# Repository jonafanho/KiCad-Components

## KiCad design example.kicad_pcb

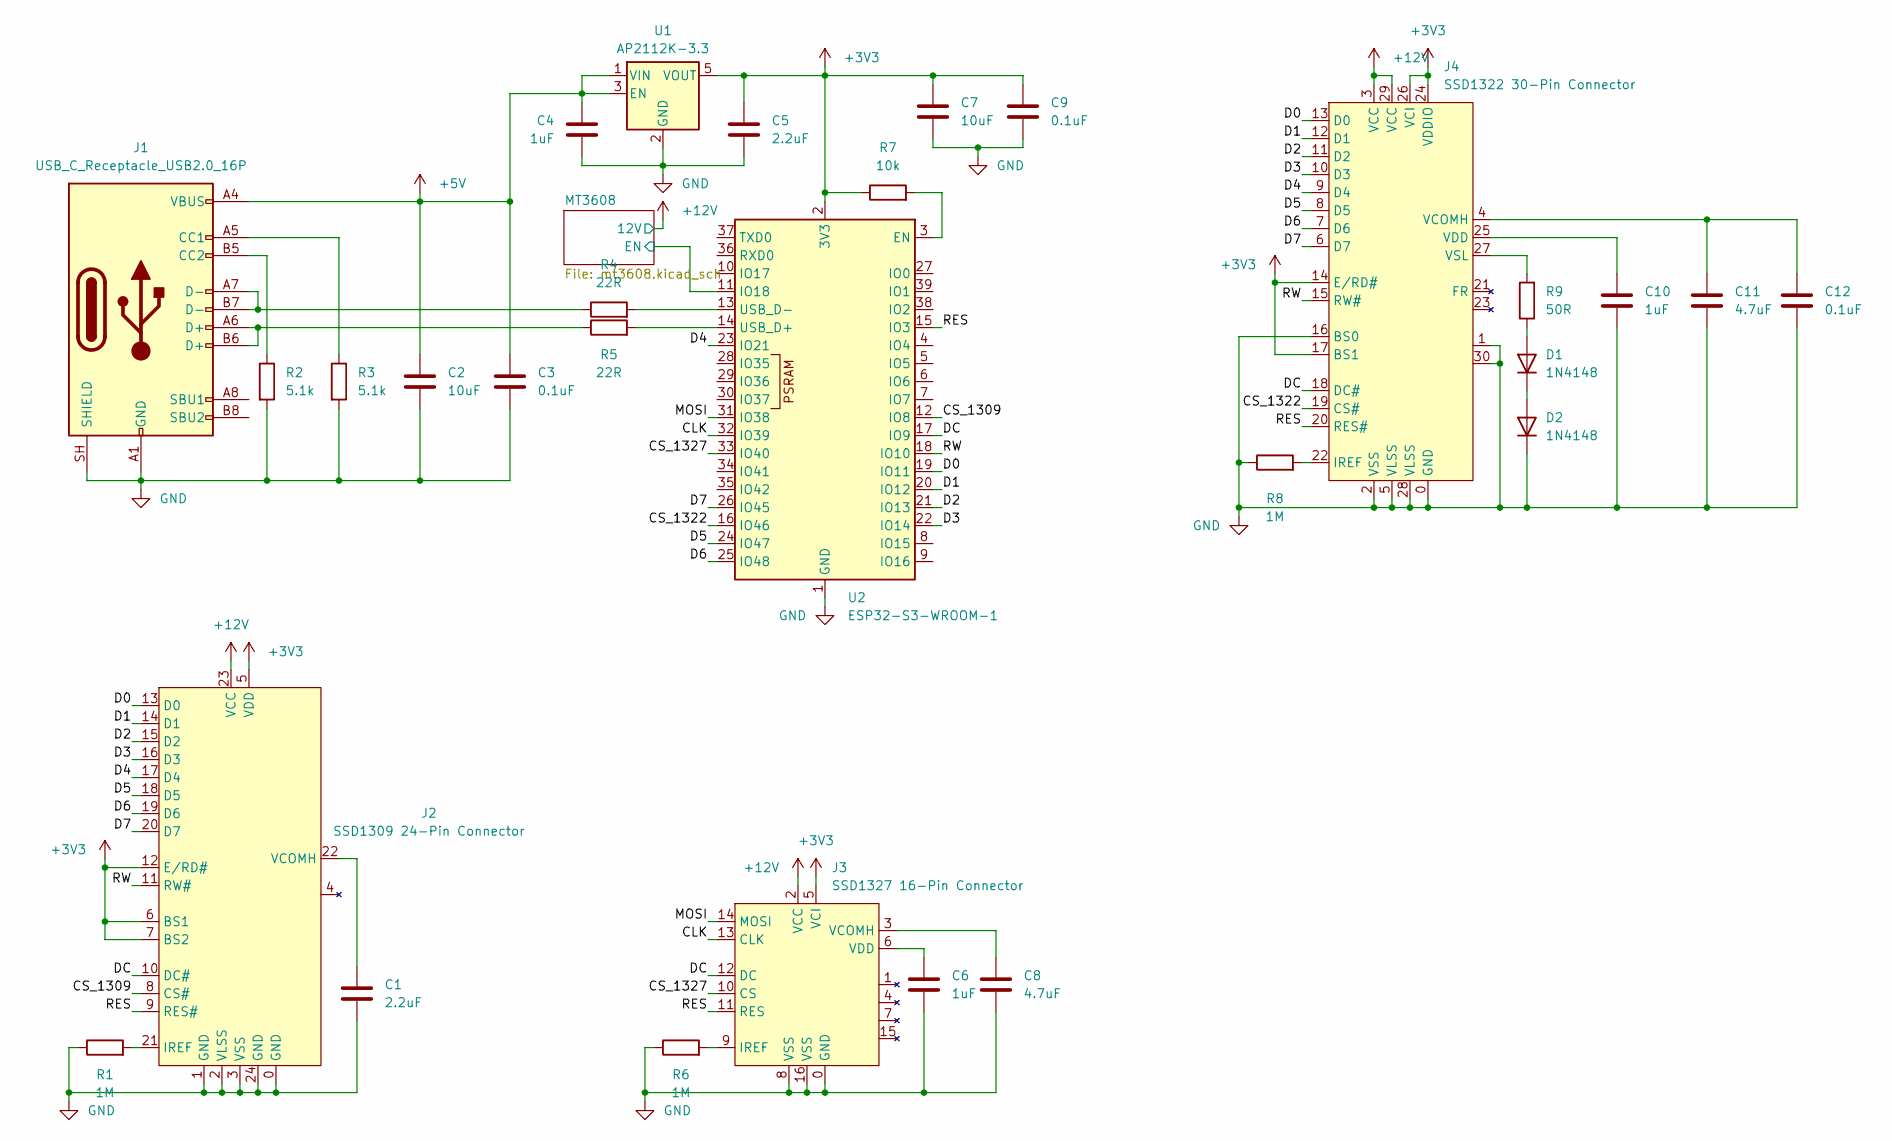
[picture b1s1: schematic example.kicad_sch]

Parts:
C1, C5: 2.2uF; C_0603_1608Metric
C2, C7: 10uF; C_0603_1608Metric
C3, C9, C12: 0.1uF; C_0603_1608Metric
C4, C6, C10: 1uF; C_0603_1608Metric
C8, C11: 4.7uF; C_0603_1608Metric
D1, D2: 1N4148; D_SOD-123
J1: USB_C_Receptacle_USB2.0_16P; USB_C_Receptacle_HCTL_HC-TYPE-C-16P-01A
J2: SSD1309 24-Pin Connector; 24-pin
J3: SSD1327 16-Pin Connector; 16-pin
J4: SSD1322 30-Pin Connector; 30-pin
R1, R6, R8: 1M; R_0603_1608Metric
R2, R3: 5.1k; R_0603_1608Metric
R4, R5: 22R; R_0603_1608Metric
R7: 10k; R_0603_1608Metric
R9: 50R; R_0603_1608Metric
U1: AP2112K-3.3; SOT-23-5
U2: ESP32-S3-WROOM-1

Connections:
+3V3: C5.1, C7.1, C9.1, J2.5 (VDD), J2.6 (BS1), J2.7 (BS2), J2.12 (E/RD#), J3.5 (VCI), J4.14 (E/RD#), J4.17 (BS1), J4.24 (VDDIO), J4.26 (VCI), R7.1, U1.5 (VOUT), U2.2 (3V3)
+5V: C2.1, C3.1, C4.1, J1.A4 (VBUS), J1.A9 (VBUS), J1.B4 (VBUS), J1.B9 (VBUS), U1.1 (VIN), U1.3 (EN); also elsewhere on the board
+12V: J2.23 (VCC), J3.2 (VCC), J4.3 (VCC), J4.29 (VCC); also elsewhere on the board
/CLK: J3.13 (CLK), U2.32 (IO39)
/CS_1309: J2.8 (CS#), U2.12 (IO8)
/CS_1322: J4.19 (CS#), U2.16 (IO46)
/CS_1327: J3.10 (CS), U2.33 (IO40)
/D0: J2.13 (D0), J4.13 (D0), U2.19 (IO11)
/D1: J2.14 (D1), J4.12 (D1), U2.20 (IO12)
/D2: J2.15 (D2), J4.11 (D2), U2.21 (IO13)
/D3: J2.16 (D3), J4.10 (D3), U2.22 (IO14)
/D4: J2.17 (D4), J4.9 (D4), U2.23 (IO21)
/D5: J2.18 (D5), J4.8 (D5), U2.24 (IO47)
/D6: J2.19 (D6), J4.7 (D6), U2.25 (IO48)
/D7: J2.20 (D7), J4.6 (D7), U2.26 (IO45)
/DC: J2.10 (DC#), J3.12 (DC), J4.18 (DC#), U2.17 (IO9)
/MOSI: J3.14 (MOSI), U2.31 (IO38)
/MT3608/EN: U2.11 (IO18); also elsewhere on the board
/RES: J2.9 (RES#), J3.11 (RES), J4.20 (RES#), U2.15 (IO3)
/RW: J2.11 (RW#), J4.15 (RW#), U2.18 (IO10)
GND: C1.2, C2.2, C3.2, C4.2, C5.2, C6.2, C7.2, C8.2, C9.2, C10.2, C11.2, C12.2, D2.1 (K), J1.A1 (GND), J1.A12 (GND), J1.B1 (GND), J1.B12 (GND), J1.SH (SHIELD), J2.0 (GND), J2.1 (GND), J2.2 (VLSS), J2.3 (VSS), J2.24 (GND), J3.0 (GND), J3.8 (VSS), J3.16 (VSS), J4.0 (GND), J4.1, J4.2 (VSS), J4.5 (VLSS), J4.16 (BS0), J4.28 (VLSS), J4.30, R1.1, R2.2, R3.2, R6.1, R8.1, U1.2 (GND), U2.1 (GND), U2.40 (GND), U2.41 (GND); also elsewhere on the board
unnamed: D1.2 (A), R9.1
unnamed: D1.1 (K), D2.2 (A)
unnamed: J1.A5 (CC1), R3.1
unnamed: J1.B5 (CC2), R2.1
unnamed: J1.A6 (D+), J1.B6 (D+), R5.1
unnamed: J1.A7 (D-), J1.B7 (D-), R4.1
unnamed: J2.21 (IREF), R1.2
unnamed: C1.1, J2.22 (VCOMH)
unnamed: J3.9 (IREF), R6.2
unnamed: C8.1, J3.3 (VCOMH)
unnamed: C6.1, J3.6 (VDD)
unnamed: J4.22 (IREF), R8.2
unnamed: C11.1, C12.1, J4.4 (VCOMH)
unnamed: C10.1, J4.25 (VDD)
unnamed: J4.27 (VSL), R9.2
unnamed: R7.2, U2.3 (EN)
unnamed: R5.2, U2.14 (USB_D+)
unnamed: R4.2, U2.13 (USB_D-)

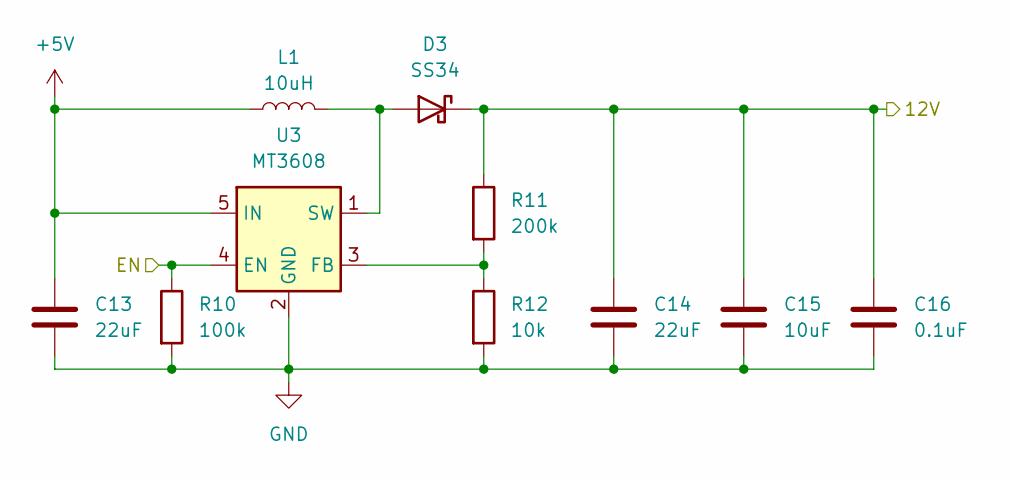
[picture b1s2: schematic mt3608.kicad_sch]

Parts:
C13, C14: 22uF; C_0805_2012Metric
C15: 10uF; C_0603_1608Metric
C16: 0.1uF; C_0603_1608Metric
D3: SS34; D_SMA
L1: 10uH; L_0603_1608Metric
R10: 100k; R_0603_1608Metric
R11: 200k; R_0603_1608Metric
R12: 10k; R_0603_1608Metric
U3: MT3608; SOT-23-6

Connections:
+5V: C13.1, L1.1, U3.5 (IN); also elsewhere on the board
+12V: C14.1, C15.1, C16.1, D3.1 (K), R11.1; also elsewhere on the board
/MT3608/EN: R10.1, U3.4 (EN); also elsewhere on the board
GND: C13.2, C14.2, C15.2, C16.2, R10.2, R12.2, U3.2 (GND); also elsewhere on the board
unnamed: D3.2 (A), L1.2, U3.1 (SW)
unnamed: R11.2, R12.1, U3.3 (FB)

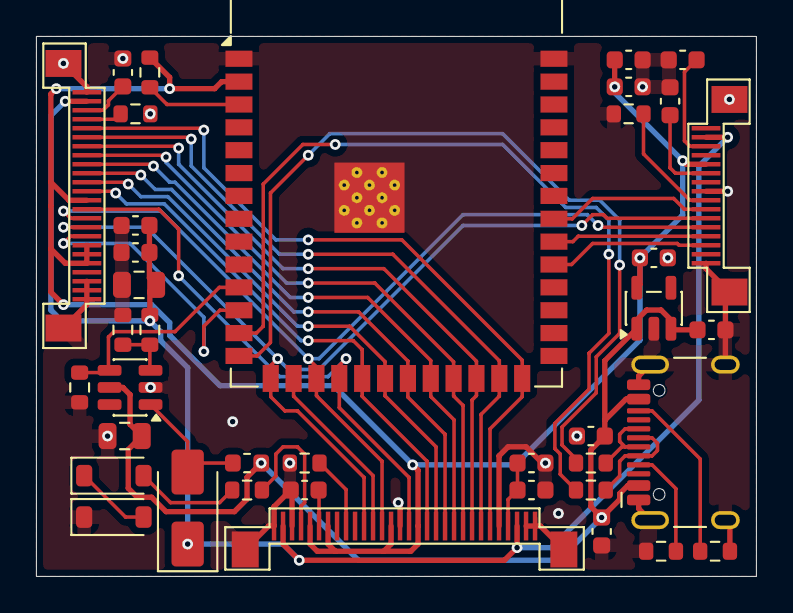
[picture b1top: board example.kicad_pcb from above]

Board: 2 copper layers, 40.0 x 30.0 mm, 39 parts (0 on the bottom side), 41 nets.
